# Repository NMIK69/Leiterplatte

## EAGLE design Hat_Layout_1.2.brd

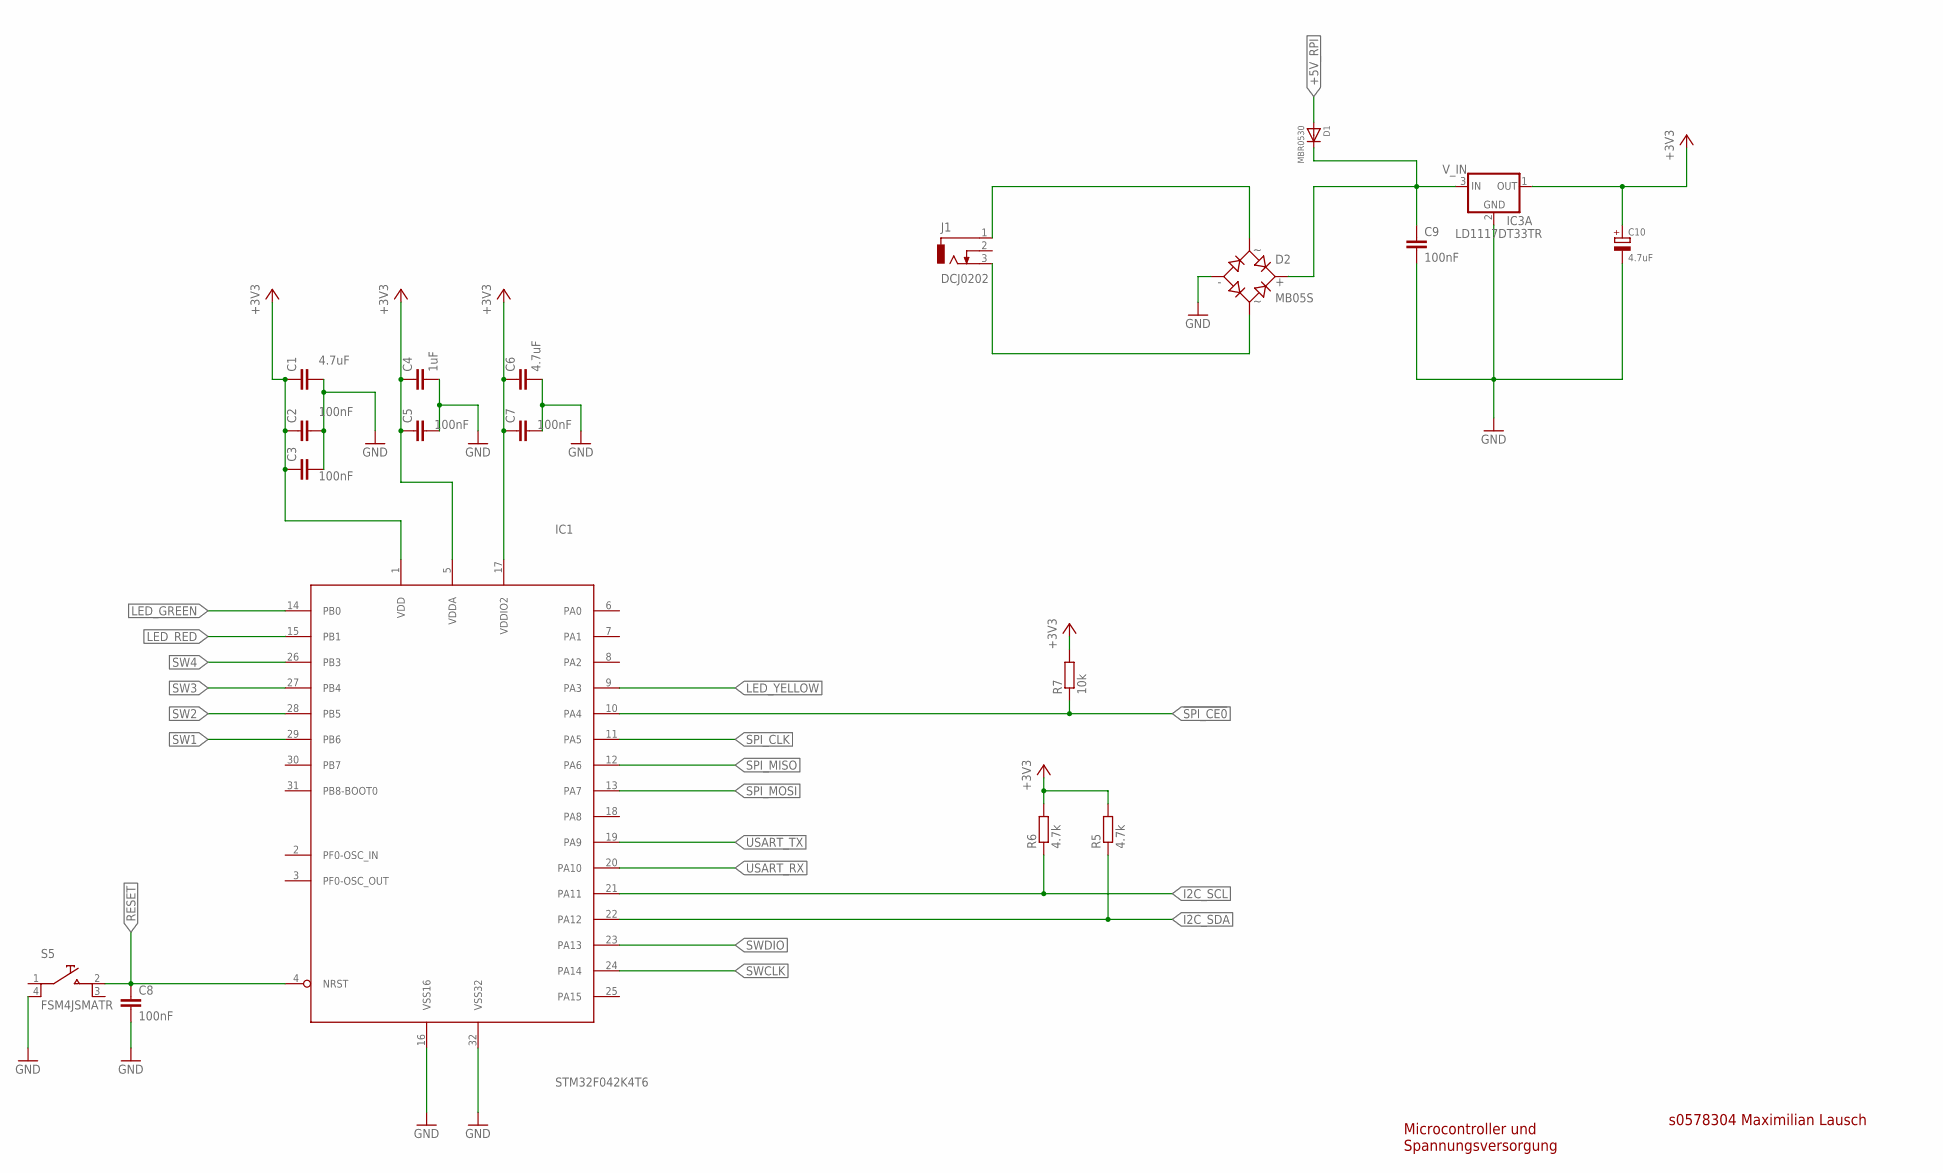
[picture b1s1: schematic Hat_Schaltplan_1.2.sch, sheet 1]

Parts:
C1, C6: 4.7uF; C0603
C2, C3, C5, C7, C8, C9: 100nF; C0603
C4: 1uF; C0603
C10: 4.7uF; WX5MM
D1: MBR0530; SOD123
D2: MB05S; MINIDIL
IC1: STM32F042K4T6; LQPF32
IC3: LD1117DT33TR; SOT89R
J1: DCJ0202
R5, R6: 4.7k; R0603
R7: 10k; R0603
S5: FSM4JSMATR

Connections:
!SPI_CE0: IC1.10 (PA4), R7.1; also elsewhere on the board
+3V3: C1.1, C2.1, C3.1, C4.1, C5.1, C6.1, C7.1, C10.+, IC1.1 (VDD), IC1.5 (VDDA), IC1.17 (VDDIO2), IC3.1 (OUT), R5.2, R6.2, R7.2; also elsewhere on the board
+5V_RPI: D1.A; also elsewhere on the board
GND: C1.2, C2.2, C3.2, C4.2, C5.2, C6.2, C7.2, C8.2, C9.2, C10.-, D2.-, IC1.16 (VSS16), IC1.32 (VSS32), IC3.2 (GND), S5.4; also elsewhere on the board
I2C_SCL: IC1.21 (PA11), R6.1; also elsewhere on the board
I2C_SDA: IC1.22 (PA12), R5.1; also elsewhere on the board
LED_GREEN: IC1.14 (PB0); also elsewhere on the board
LED_RED: IC1.15 (PB1); also elsewhere on the board
LED_YELLOW: IC1.9 (PA3); also elsewhere on the board
unnamed: D2.4 (AC2), J1.3
unnamed: D2.3 (AC1), J1.1
RESET: C8.1, IC1.4 (NRST), S5.2; also elsewhere on the board
SPI_CLK: IC1.11 (PA5); also elsewhere on the board
SPI_MISO: IC1.12 (PA6); also elsewhere on the board
SPI_MOSI: IC1.13 (PA7); also elsewhere on the board
SW1: IC1.29 (PB6); also elsewhere on the board
SW2: IC1.28 (PB5); also elsewhere on the board
SW3: IC1.27 (PB4); also elsewhere on the board
SW4: IC1.26 (PB3); also elsewhere on the board
SWCLK: IC1.24 (PA14); also elsewhere on the board
SWDIO: IC1.23 (PA13); also elsewhere on the board
USART_RX: IC1.20 (PA10); also elsewhere on the board
USART_TX: IC1.19 (PA9); also elsewhere on the board
V_IN: C9.1, D1.K, D2.+, IC3.3 (IN)

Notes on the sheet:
s0578304 Maximilian Lausch
Microcontroller und Spannungsversorgung

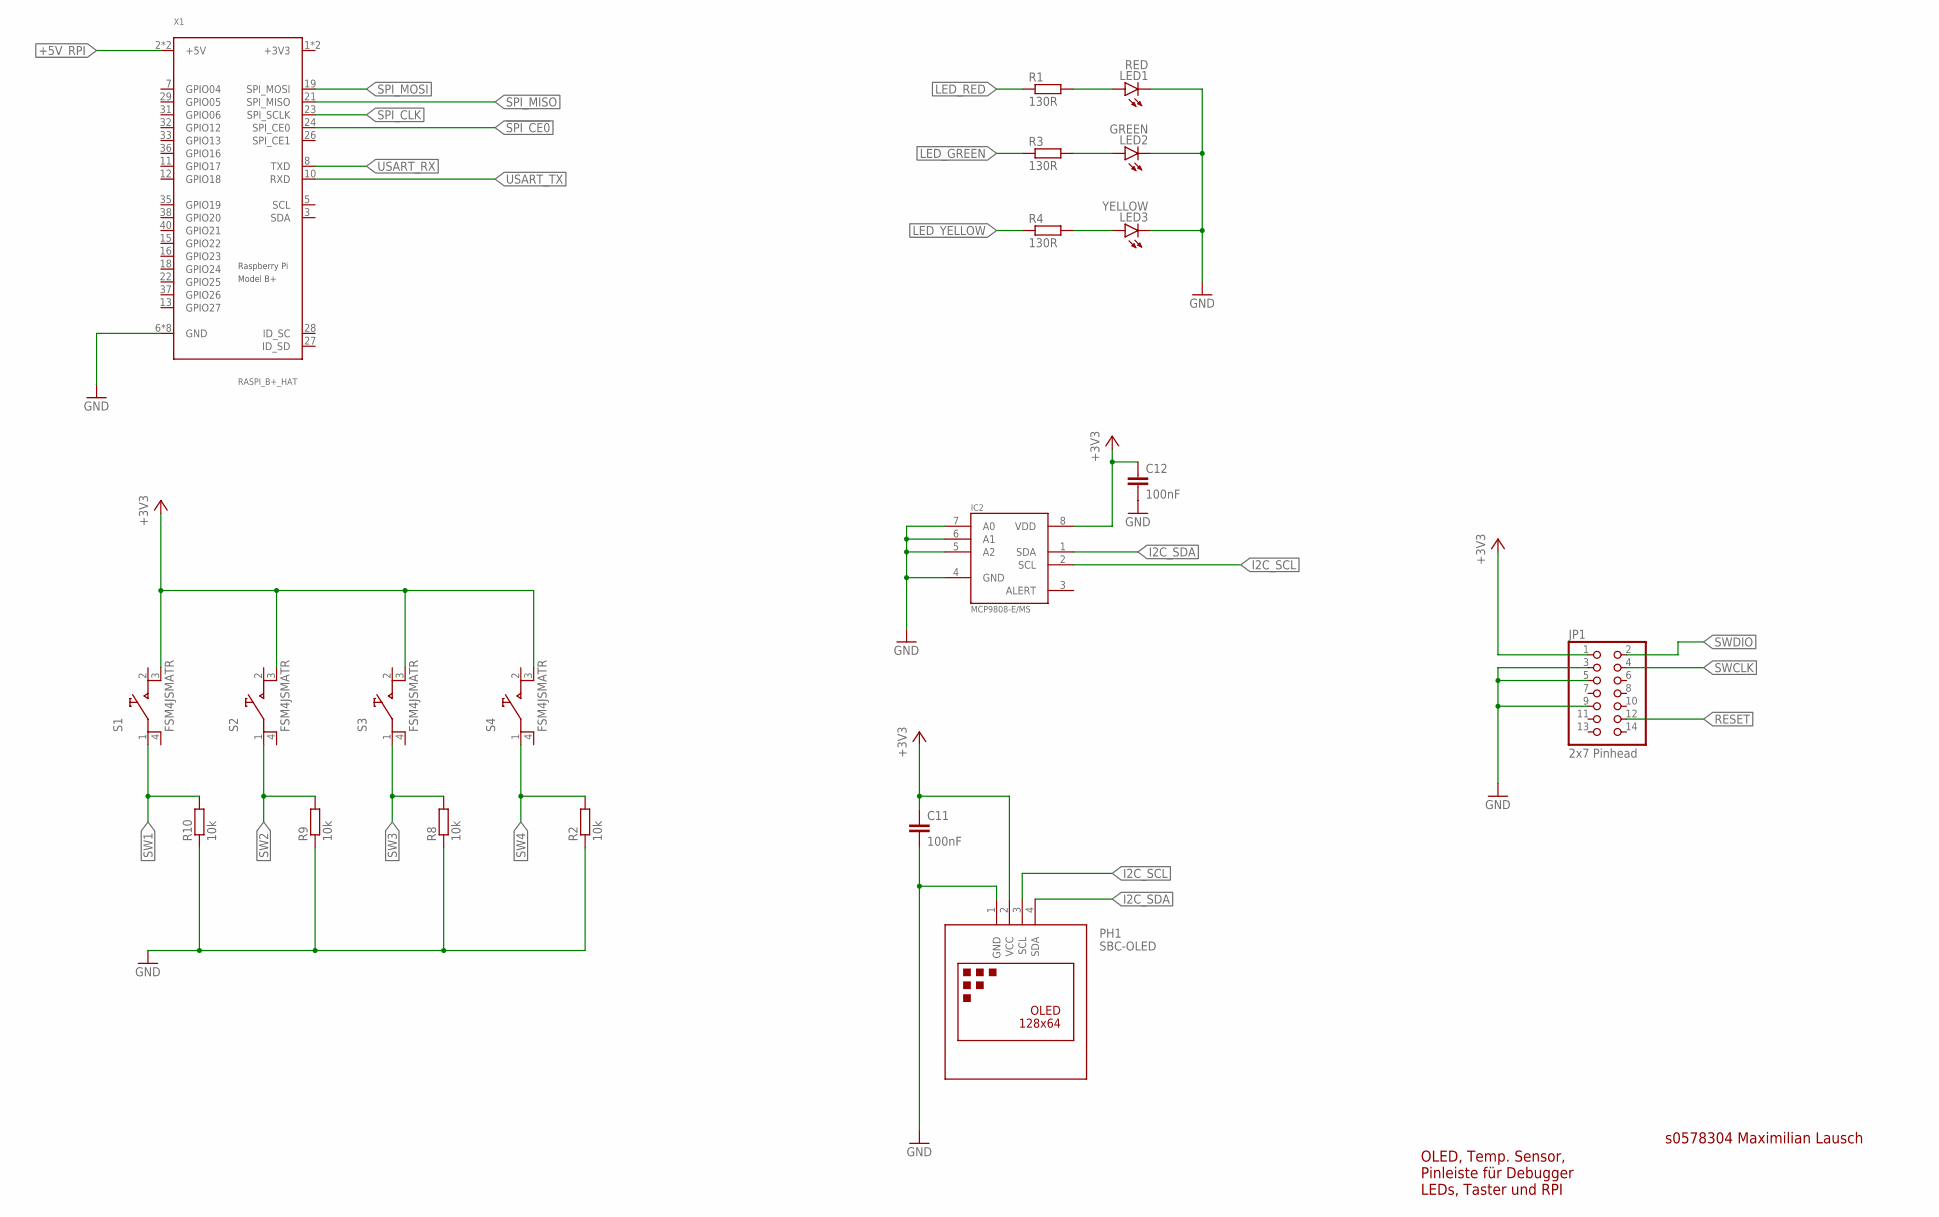
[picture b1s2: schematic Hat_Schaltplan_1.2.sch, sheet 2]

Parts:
C11, C12: 100nF; C0603
IC2: MCP9808-E/MS; MSOP8_0.65MM
JP1: 2x7 Pinhead; 2X07
LED1: RED; SMARTLED-TTW
LED2: GREEN; SMARTLED-TTW
LED3: YELLOW; SMARTLED-TTW
PH1: SBC-OLED; DISPLAY-OLED-128X64-I2C
R1, R3, R4: 130R; R0603
R2, R8, R9, R10: 10k; R0603
S1, S2, S3, S4: FSM4JSMATR
X1: RASPI_B+_HAT; RASPI_BOARD_B+HAT

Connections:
!SPI_CE0: X1.24 (SPI_CE0); also elsewhere on the board
+3V3: C11.1, C12.1, IC2.8 (VDD), JP1.1, PH1.2 (VCC), S1.3, S2.3, S3.3, S4.3, X1.1 (+3V3), X1.17 (+3V3); also elsewhere on the board
+5V_RPI: X1.2 (+5V), X1.4 (+5V); also elsewhere on the board
GND: C11.2, C12.2, IC2.4 (GND), IC2.5 (A2), IC2.6 (A1), IC2.7 (A0), JP1.3, JP1.5, JP1.9, LED1.C@1 (C), LED2.C@1 (C), LED3.C@1 (C), PH1.1 (GND), R2.1, R8.1, R9.1, R10.1, X1.6 (GND), X1.9 (GND), X1.14 (GND), X1.20 (GND), X1.25 (GND), X1.30 (GND), X1.34 (GND), X1.39 (GND); also elsewhere on the board
I2C_SCL: IC2.2 (SCL), PH1.3 (SCL); also elsewhere on the board
I2C_SDA: IC2.1 (SDA), PH1.4 (SDA); also elsewhere on the board
LED_GREEN: R3.1; also elsewhere on the board
LED_RED: R1.1; also elsewhere on the board
LED_YELLOW: R4.1; also elsewhere on the board
unnamed: LED1.A@1 (A), R1.2
unnamed: LED2.A@1 (A), R3.2
unnamed: LED3.A@1 (A), R4.2
RESET: JP1.12; also elsewhere on the board
SPI_CLK: X1.23 (SPI_SCLK); also elsewhere on the board
SPI_MISO: X1.21 (SPI_MISO); also elsewhere on the board
SPI_MOSI: X1.19 (SPI_MOSI); also elsewhere on the board
SW1: R10.2, S1.1; also elsewhere on the board
SW2: R9.2, S2.1; also elsewhere on the board
SW3: R8.2, S3.1; also elsewhere on the board
SW4: R2.2, S4.1; also elsewhere on the board
SWCLK: JP1.4; also elsewhere on the board
SWDIO: JP1.2; also elsewhere on the board
USART_RX: X1.8 (TXD); also elsewhere on the board
USART_TX: X1.10 (RXD); also elsewhere on the board

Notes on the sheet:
s0578304 Maximilian Lausch
OLED, Temp. Sensor, Pinleiste für Debugger LEDs, Taster und RPI

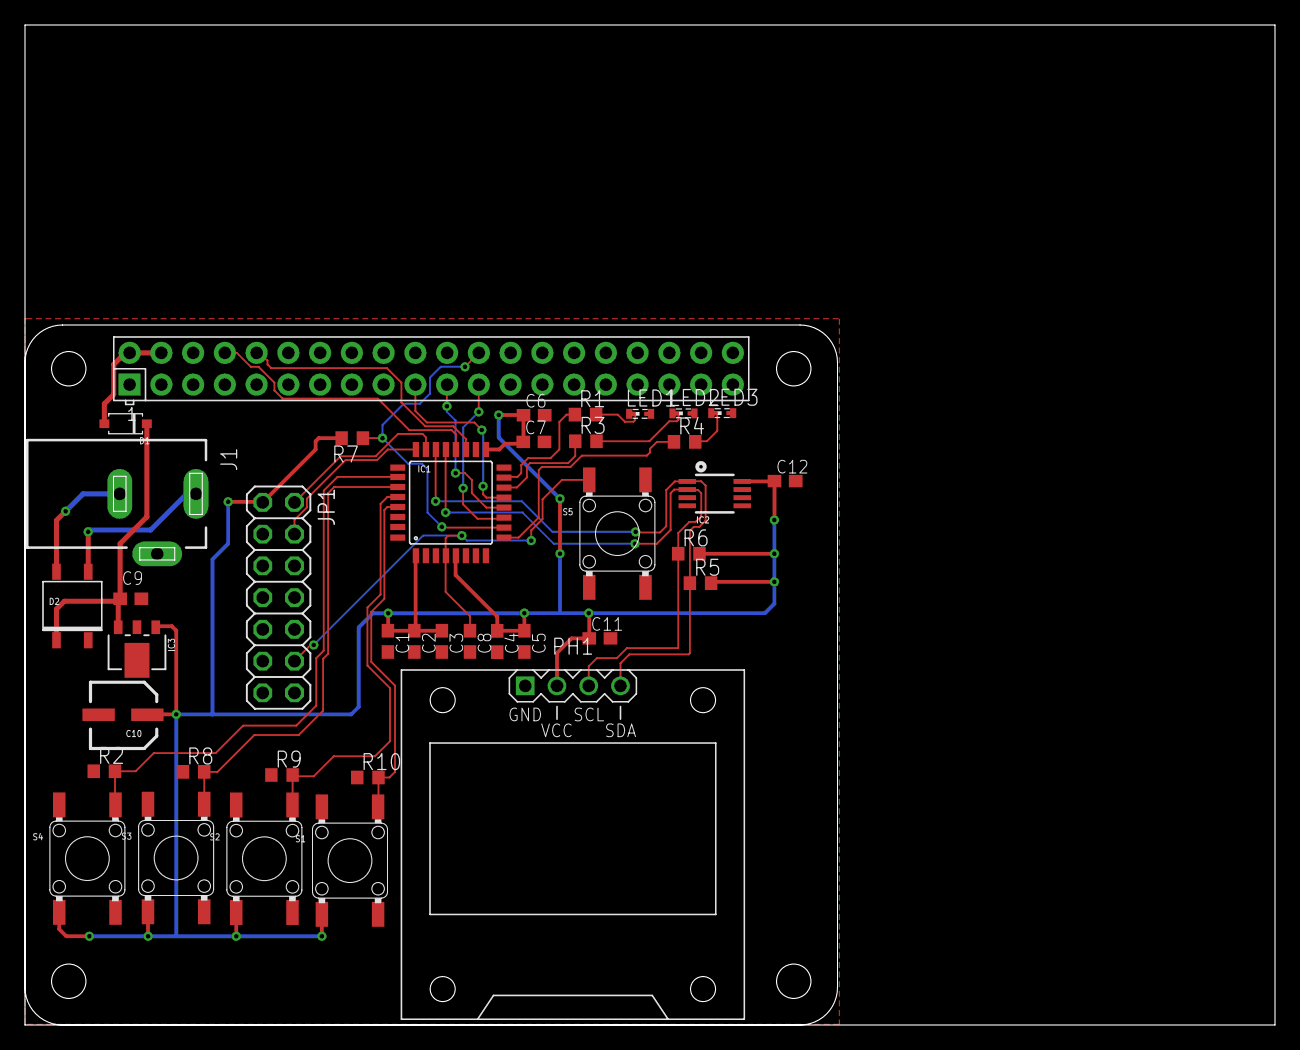
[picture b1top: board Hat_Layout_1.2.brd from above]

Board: 2 copper layers, 100.0 x 80.0 mm, 39 parts (0 on the bottom side), 27 nets.

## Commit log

2022-11-04 Schaltplan and Layout
